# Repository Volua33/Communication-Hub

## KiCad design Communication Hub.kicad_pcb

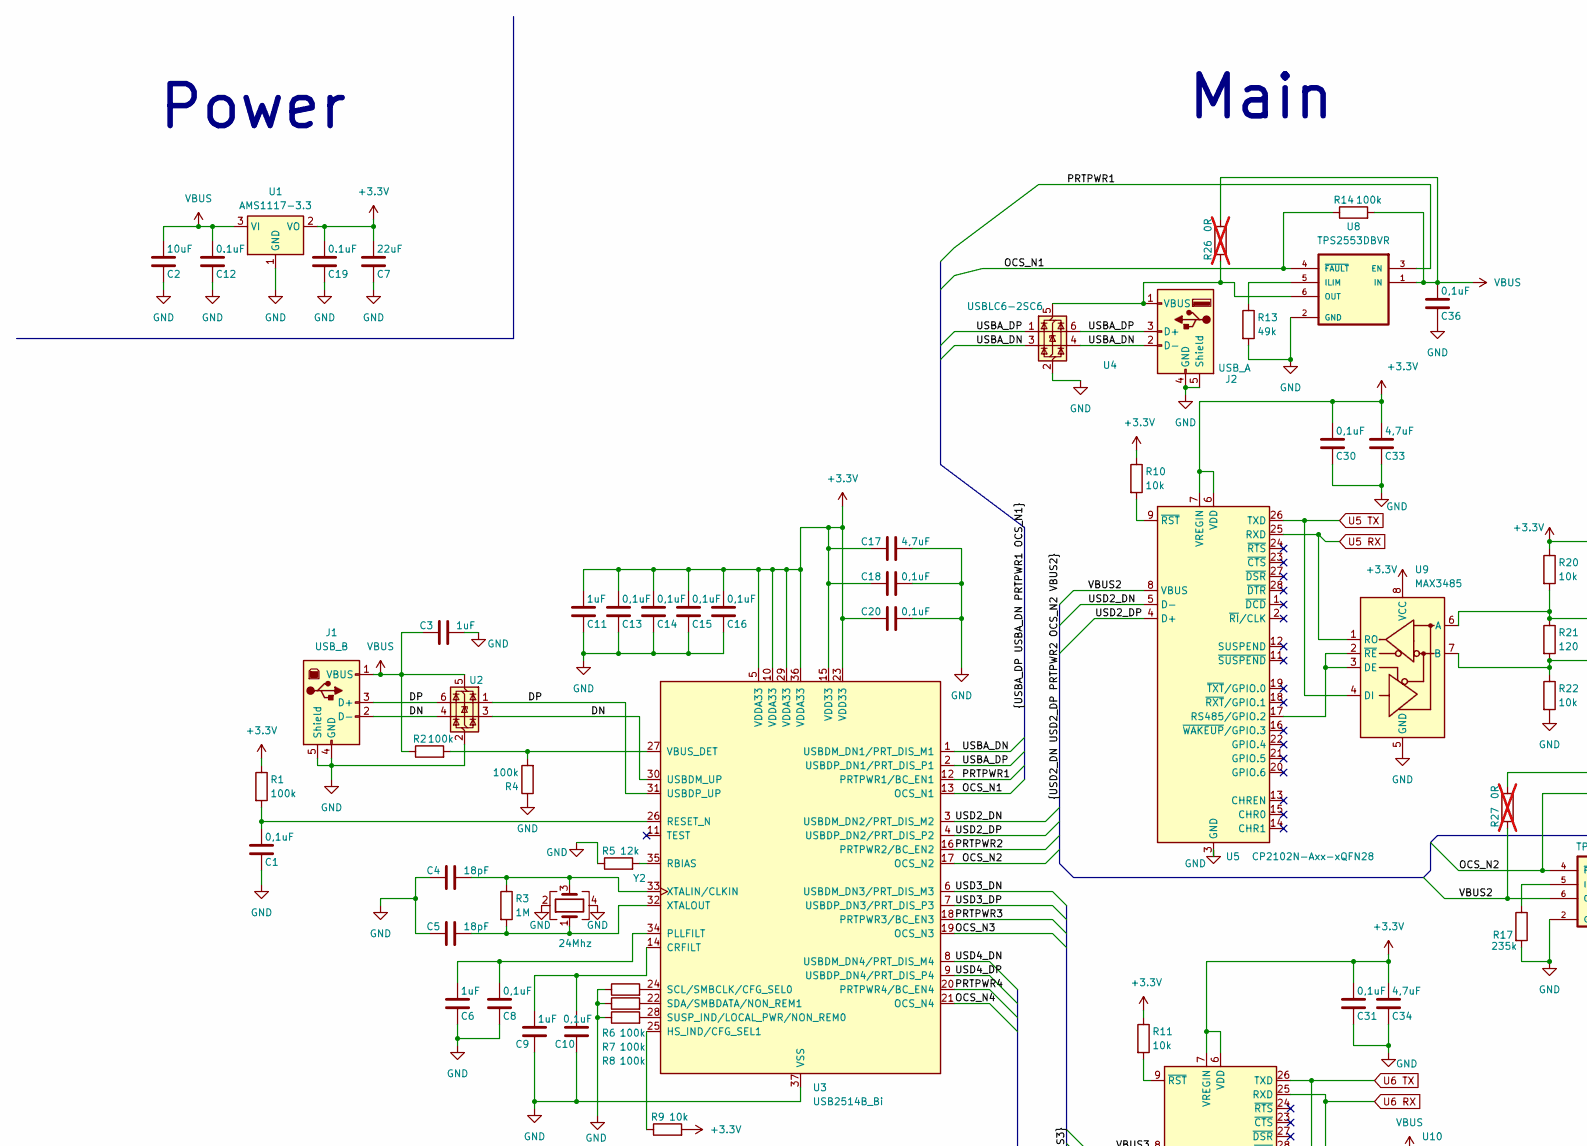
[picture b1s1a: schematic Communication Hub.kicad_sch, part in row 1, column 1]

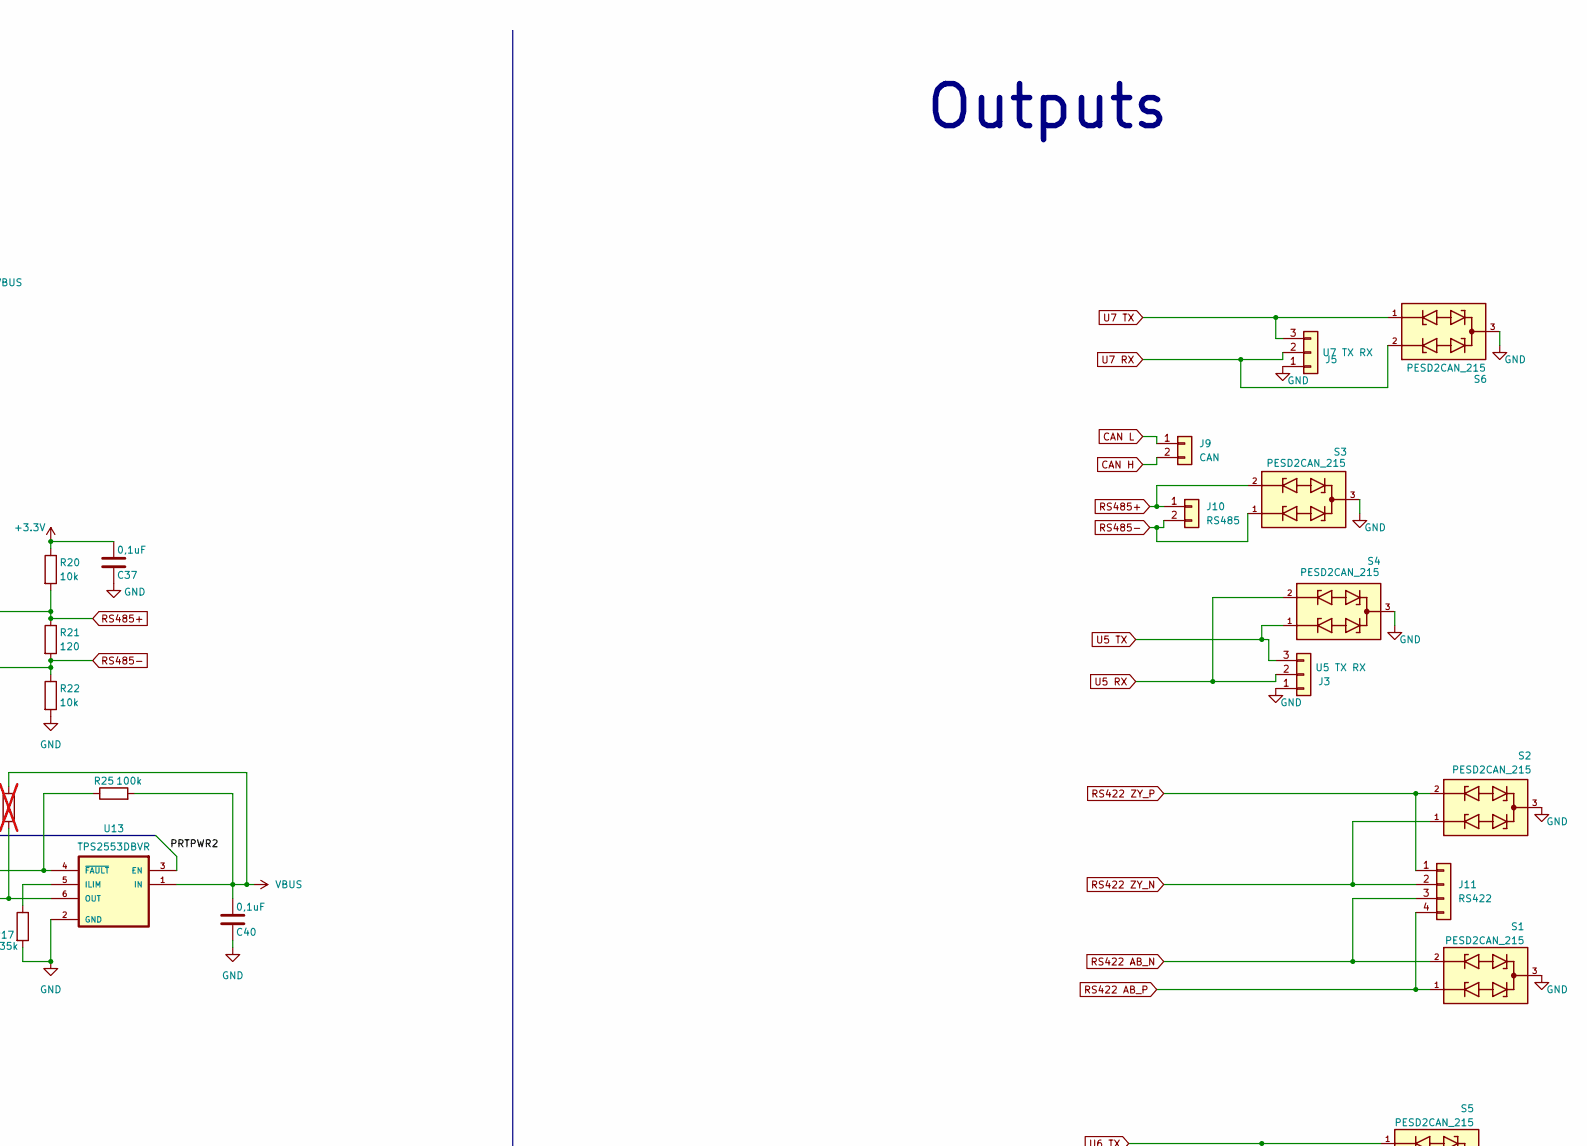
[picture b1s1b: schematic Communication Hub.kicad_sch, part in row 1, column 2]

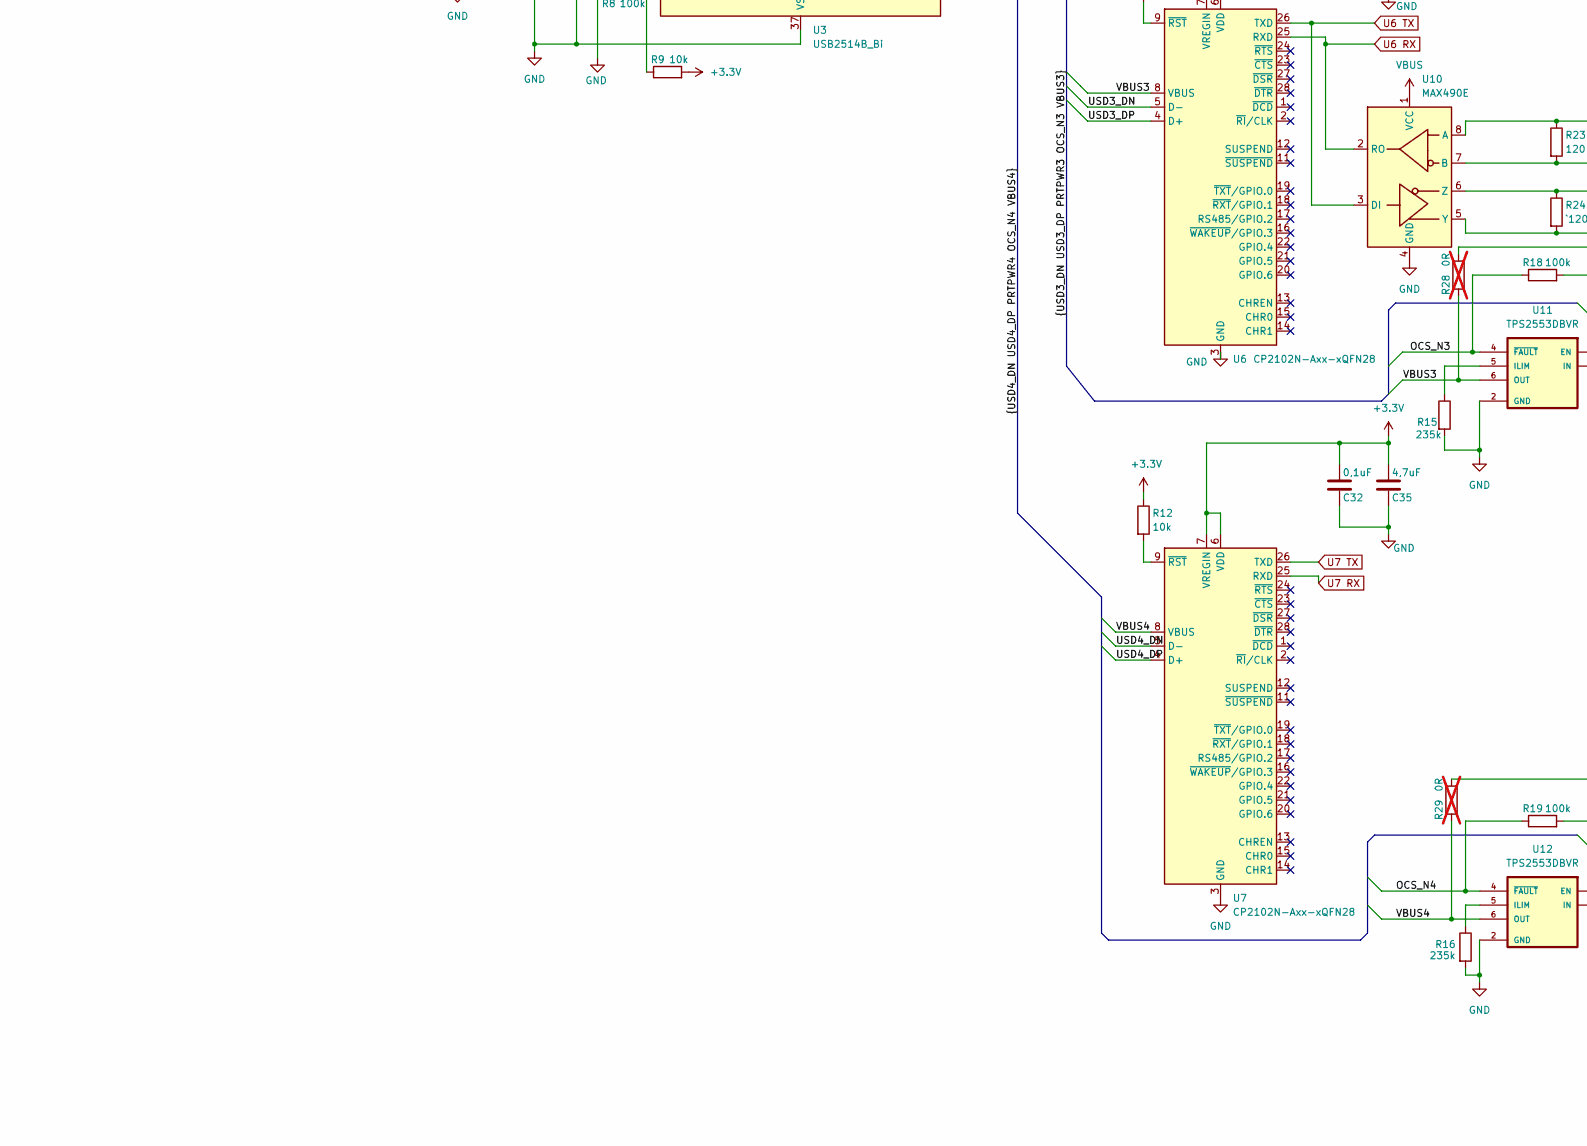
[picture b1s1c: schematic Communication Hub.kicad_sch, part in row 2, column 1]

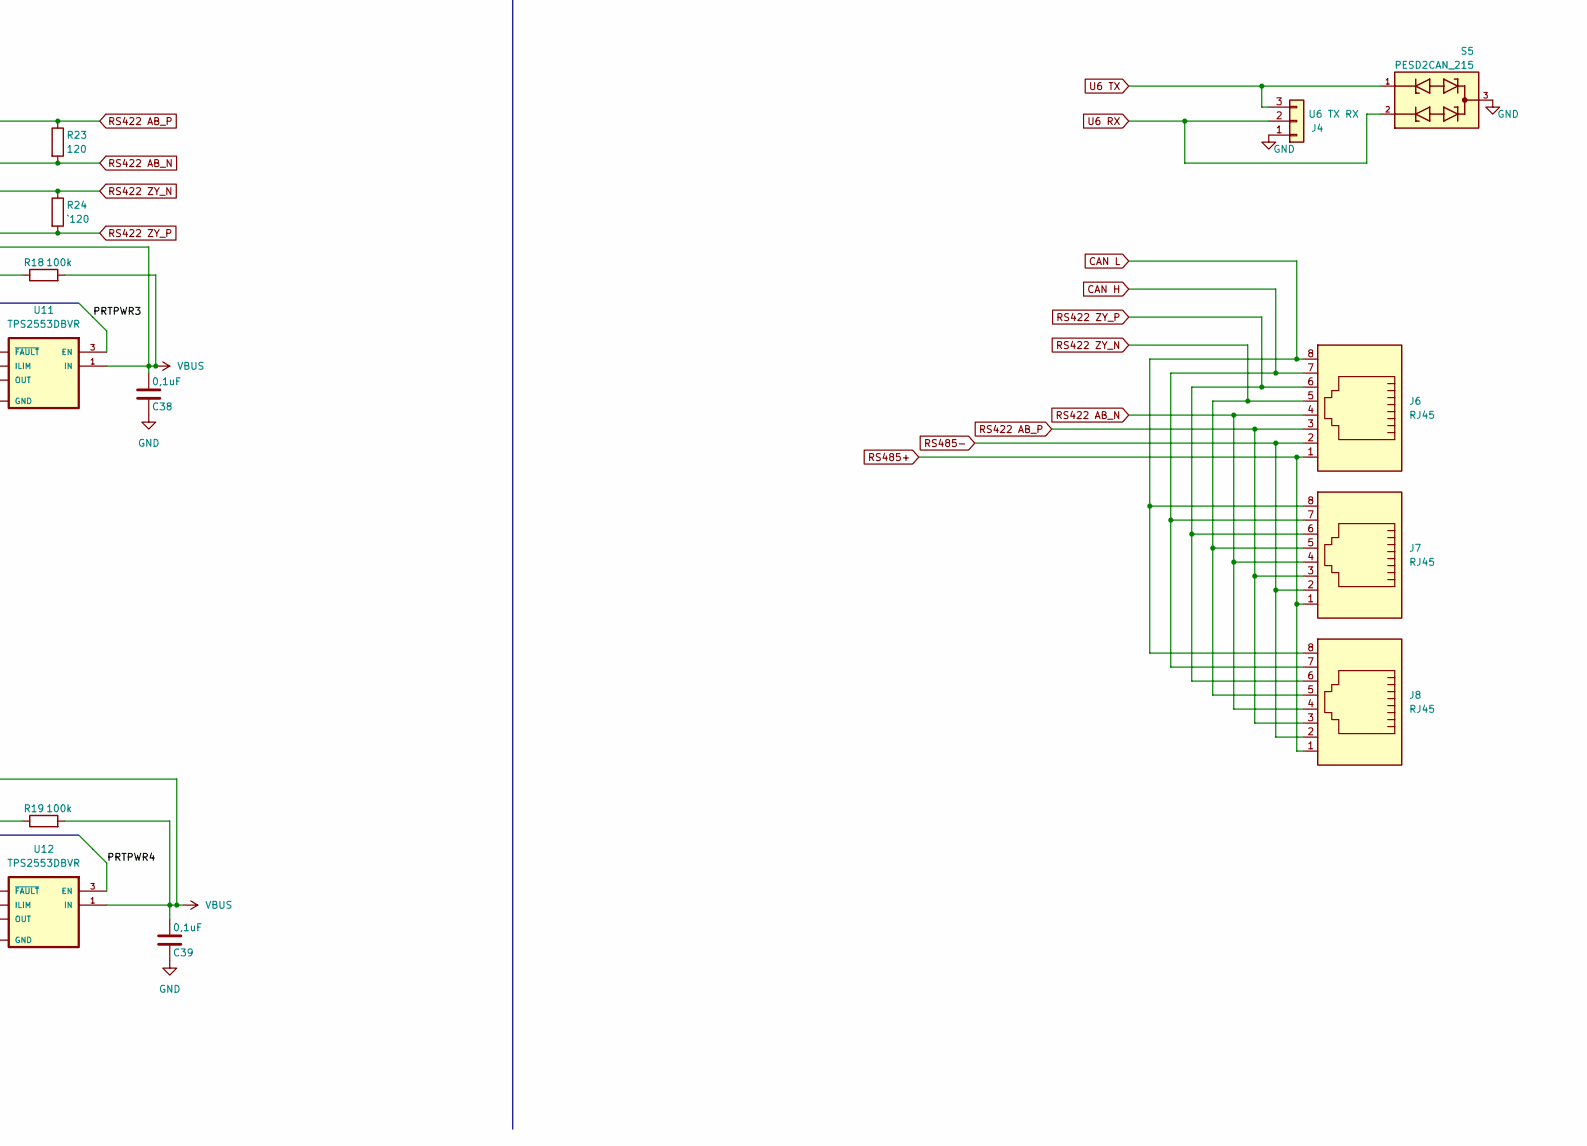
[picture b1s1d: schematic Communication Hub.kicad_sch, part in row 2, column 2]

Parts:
C1, C8, C10, C13, C14, C15, C16, C18, C20, C30, C31, C32, C36, C37, C38, C39, C40: 0,1uF; C_0603_1608Metric
C2: 10uF; CP_Radial_D4.0mm_P1.50mm
C3, C6, C9, C11: 1uF; C_0603_1608Metric
C4, C5: 18pF; C_0603_1608Metric
C7: 22uF; CP_Radial_D4.0mm_P1.50mm
C12, C19: 0.1uF; C_0603_1608Metric
C17, C33, C34, C35: 4,7uF; C_0603_1608Metric
J1: USB_B; USB_B_Lumberg_2411_02_Horizontal
J2: USB_A; USB_A_Connfly_DS1095
J3: U5 TX RX; PinHeader_1x03_P2.54mm_Vertical
J4: U6 TX RX; PinHeader_1x03_P2.54mm_Vertical
J5: U7 TX RX; PinHeader_1x03_P2.54mm_Vertical
J6, J7, J8: RJ45; RJ45_OST_PJ012-8P8CX_Vertical
J9: CAN; PinHeader_1x02_P2.54mm_Vertical
J10: RS485; PinHeader_1x02_P2.54mm_Vertical
J11: RS422; PinHeader_1x04_P2.54mm_Vertical
R1, R2, R4, R6, R7, R8, R14, R18, R19, R25: 100k; R_0603_1608Metric
R3: 1M; R_0603_1608Metric
R5: 12k; R_0603_1608Metric
R9, R10, R11, R12, R20, R22: 10k; R_0603_1608Metric
R13: 49k; R_0603_1608Metric
R15, R16, R17: 235k; R_0603_1608Metric
R21, R23: 120; R_0603_1608Metric
R24: `120; R_0603_1608Metric
R26, R27, R28, R29: 0R; R_0603_1608Metric; not fitted
S1, S2, S3, S4, S5, S6: PESD2CAN_215; DIO_PESD2CAN_215
U1: AMS1117-3.3; SOT-223-3_TabPin2
U2, U4: USBLC6-2SC6; SOT-23-6
U3: USB2514B_Bi; QFN-36-1EP_6x6mm_P0.5mm_EP3.7x3.7mm
U5, U6, U7: CP2102N-Axx-xQFN28; QFN-28-1EP_5x5mm_P0.5mm_EP3.35x3.35mm
U8, U11, U12, U13: TPS2553DBVR; SOT95P280X145-6N
U9: MAX3485; SOIC-8_3.9x4.9mm_P1.27mm
U10: MAX490E; SOIC-8_3.9x4.9mm_P1.27mm
Y2: 24Mhz; Crystal_SMD_5032-4Pin_5.0x3.2mm

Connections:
+3.3V: C7.2, C11.2, C13.2, C14.2, C15.2, C16.2, C17.1, C18.1, C19.2, C20.1, C30.2, C31.2, C32.2, C33.2, C34.2, C35.2, C37.2, R1.1, R9.2, R10.1, R11.1, R12.1, R20.1, U1.2 (VO), U3.5 (VDDA33), U3.10 (VDDA33), U3.15 (VDD33), U3.23 (VDD33), U3.29 (VDDA33), U3.36 (VDDA33), U5.6 (VDD), U5.7 (VREGIN), U6.6 (VDD), U6.7 (VREGIN), U7.6 (VDD), U7.7 (VREGIN), U9.8 (VCC)
/DN: J1.2 (D-), U2.3 (I/O2), U2.4 (I/O2), U3.30 (USBDM_UP)
/DP: J1.3 (D+), U2.1 (I/O1), U2.6 (I/O1), U3.31 (USBDP_UP)
CAN H: J6.7, J7.7, J8.7, J9.2
CAN L: J6.8, J7.8, J8.8, J9.1
GND: C1.1, C2.1, C3.2, C4.1, C5.1, C6.1, C7.1, C8.1, C9.1, C10.1, C11.1, C12.1, C13.1, C14.1, C15.1, C16.1, C17.2, C18.2, C19.1, C20.2, C30.1, C31.1, C32.1, C33.1, C34.1, C35.1, C36.1, C37.1, C38.1, C39.1, C40.1, J1.4 (GND), J1.5 (Shield), J2.4 (GND), J2.5 (Shield), J3.1, J4.1, J5.1, R4.1, R5.1, R6.1, R7.1, R8.1, R13.2, R15.2, R16.2, R17.2, R22.2, S1.3, S2.3, S3.3, S4.3, S5.3, S6.3, U1.1 (GND), U2.2 (GND), U3.37 (VSS), U4.2 (GND), U5.3 (GND), U5.29 (GND), U6.3 (GND), U6.29 (GND), U7.3 (GND), U7.29 (GND), U8.2 (GND), U9.5 (GND), U10.4 (GND), U11.2 (GND), U12.2 (GND), U13.2 (GND), Y2.2, Y2.4
unnamed: J2.1 (VBUS), R26.1, U4.5 (VBUS), U8.6 (OUT)
unnamed: C9.2, C10.2, U3.14 (CRFILT)
unnamed: R9.1, U3.25 (HS_IND/CFG_SEL1)
unnamed: C6.2, C8.2, U3.34 (PLLFILT)
unnamed: R5.2, U3.35 (RBIAS)
unnamed: C1.2, R1.2, U3.26 (RESET_N)
unnamed: R6.2, U3.24 (SCL/SMBCLK/CFG_SEL0)
unnamed: R7.2, U3.22 (SDA/SMBDATA/NON_REM1)
unnamed: R8.2, U3.28 (SUSP_IND/LOCAL_PWR/NON_REM0)
unnamed: R2.2, R4.2, U3.27 (VBUS_DET)
unnamed: C4.2, R3.1, U3.33 (XTALIN/CLKIN), Y2.3
unnamed: C5.2, R3.2, U3.32 (XTALOUT), Y2.1
unnamed: U5.17 (RS485/GPIO.2), U9.2 (~RE), U9.3 (DE)
unnamed: R10.2, U5.9 (~RST)
unnamed: R11.2, U6.9 (~RST)
unnamed: R12.2, U7.9 (~RST)
unnamed: R13.1, U8.5 (ILIM)
unnamed: R15.1, U11.5 (ILIM)
unnamed: R16.1, U12.5 (ILIM)
unnamed: R17.1, U13.5 (ILIM)
OCS_N1: R14.1, U3.13 (OCS_N1), U8.4 (~FAULT)
OCS_N2: R25.1, U3.17 (OCS_N2), U13.4 (~FAULT)
OCS_N3: R18.1, U3.19 (OCS_N3), U11.4 (~FAULT)
OCS_N4: R19.1, U3.21 (OCS_N4), U12.4 (~FAULT)
PRTPWR1: U3.12 (PRTPWR1/BC_EN1), U8.3 (EN)
PRTPWR2: U3.16 (PRTPWR2/BC_EN2), U13.3 (EN)
PRTPWR3: U3.18 (PRTPWR3/BC_EN3), U11.3 (EN)
PRTPWR4: U3.20 (PRTPWR4/BC_EN4), U12.3 (EN)
RS422 AB_N: J6.4, J7.4, J8.4, J11.3, R23.2, S1.2, U10.7 (B)
RS422 AB_P: J6.3, J7.3, J8.3, J11.4, R23.1, S1.1, U10.8 (A)
RS422 ZY_N: J6.5, J7.5, J8.5, J11.2, R24.1, S2.1, U10.6 (Z)
RS422 ZY_P: J6.6, J7.6, J8.6, J11.1, R24.2, S2.2, U10.5 (Y)
RS485+: J6.1, J7.1, J8.1, J10.1, R20.2, R21.1, S3.2, U9.6 (A)
RS485-: J6.2, J7.2, J8.2, J10.2, R21.2, R22.1, S3.1, U9.7 (B)
U5 RX: J3.2, S4.2, U5.25 (RXD), U9.1 (RO)
U5 TX: J3.3, S4.1, U5.26 (TXD), U9.4 (DI)
U6 RX: J4.2, S5.2, U6.25 (RXD), U10.2 (RO)
U6 TX: J4.3, S5.1, U6.26 (TXD), U10.3 (DI)
U7 RX: J5.2, S6.2, U7.25 (RXD)
U7 TX: J5.3, S6.1, U7.26 (TXD)
USBA_DN: J2.2 (D-), U3.1 (USBDM_DN1/PRT_DIS_M1), U4.3 (I/O2), U4.4 (I/O2)
USBA_DP: J2.3 (D+), U3.2 (USBDP_DN1/PRT_DIS_P1), U4.1 (I/O1), U4.6 (I/O1)
USD2_DN: U3.3 (USBDM_DN2/PRT_DIS_M2), U5.5 (D-)
USD2_DP: U3.4 (USBDP_DN2/PRT_DIS_P2), U5.4 (D+)
USD3_DN: U3.6 (USBDM_DN3/PRT_DIS_M3), U6.5 (D-)
USD3_DP: U3.7 (USBDP_DN3/PRT_DIS_P3), U6.4 (D+)
USD4_DN: U3.8 (USBDM_DN4/PRT_DIS_M4), U7.5 (D-)
USD4_DP: U3.9 (USBDP_DN4/PRT_DIS_P4), U7.4 (D+)
VBUS: C2.2, C3.1, C12.2, C36.2, C38.2, C39.2, C40.2, J1.1 (VBUS), R2.1, R14.2, R18.2, R19.2, R25.2, R26.2, R27.2, R28.2, R29.2, U1.3 (VI), U2.5 (VBUS), U8.1 (IN), U10.1 (VCC), U11.1 (IN), U12.1 (IN), U13.1 (IN)
VBUS2: R27.1, U5.8 (VBUS), U13.6 (OUT)
VBUS3: R28.1, U6.8 (VBUS), U11.6 (OUT)
VBUS4: R29.1, U7.8 (VBUS), U12.6 (OUT)

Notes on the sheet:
Outputs
Power
Main

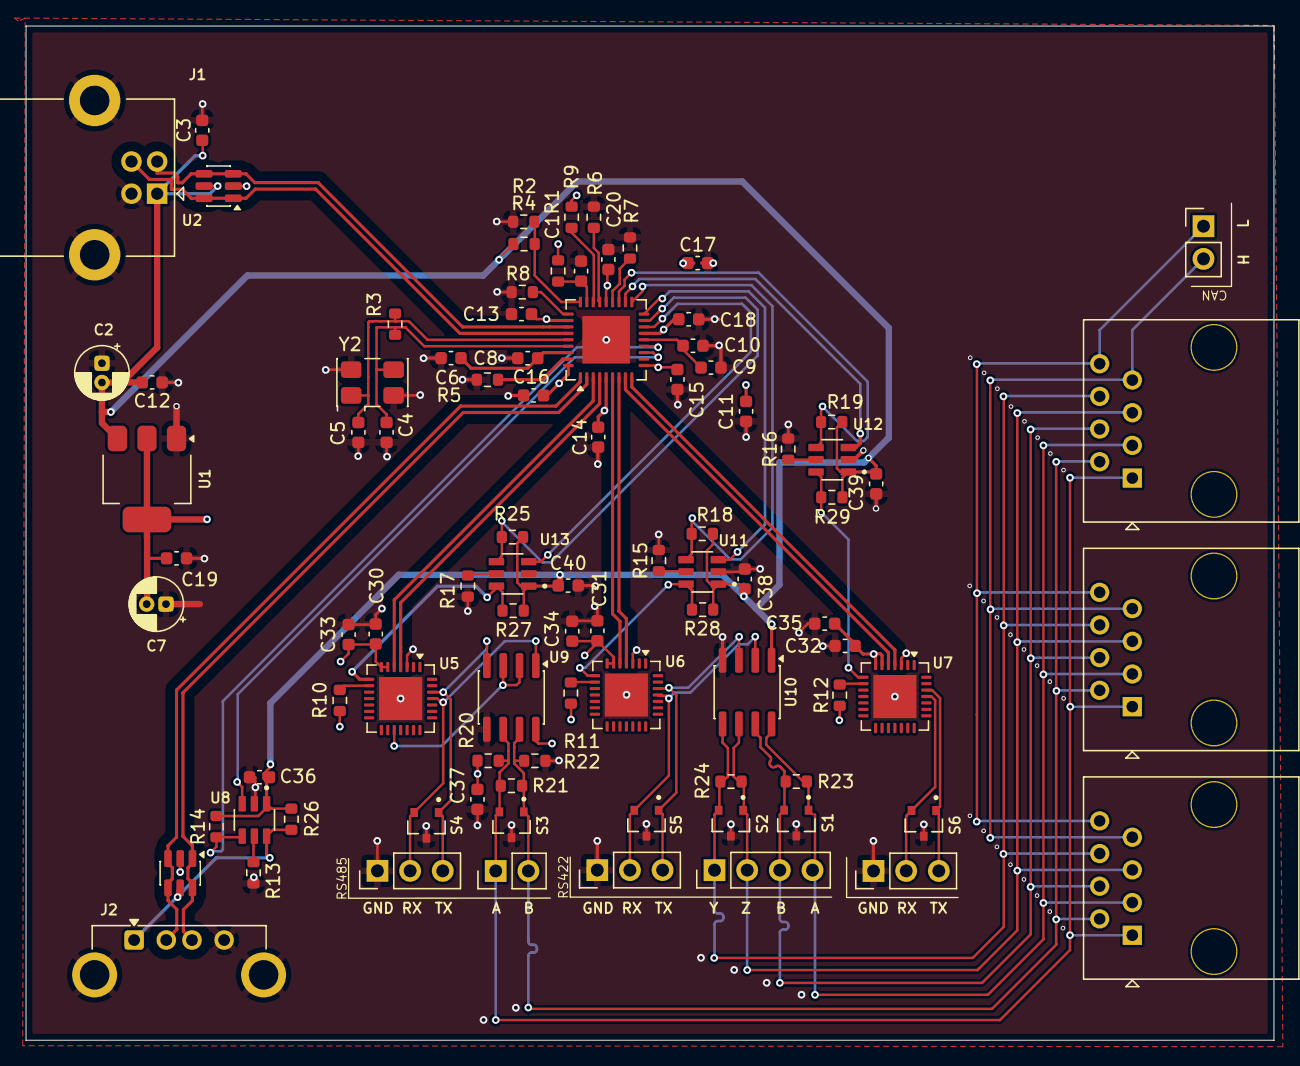
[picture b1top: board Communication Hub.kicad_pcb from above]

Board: 4 copper layers, 97.0 x 78.9 mm, 91 parts (0 on the bottom side), 58 nets.

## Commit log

2025-11-10 Initial Kicad project commit
2025-11-17 Updates to schematics and pcb
2025-11-17 updated pdf file of schematis
2025-11-22 major update to pcb and corrections to schematics
2025-11-23 Corrections to PCB
2025-11-26 Corrections to PCB (modified passive components size) Corrections to schematics(addes some capacitors and other corrections)
2025-11-30 Corrections to PCB (size optimization)
2025-12-01 Schematics reorganized
2025-12-01 Schematics reorganized and PCB size optimized
